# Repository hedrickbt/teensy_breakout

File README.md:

# teensy_breakout
CE Breakout board for the Teensy 3.2

.

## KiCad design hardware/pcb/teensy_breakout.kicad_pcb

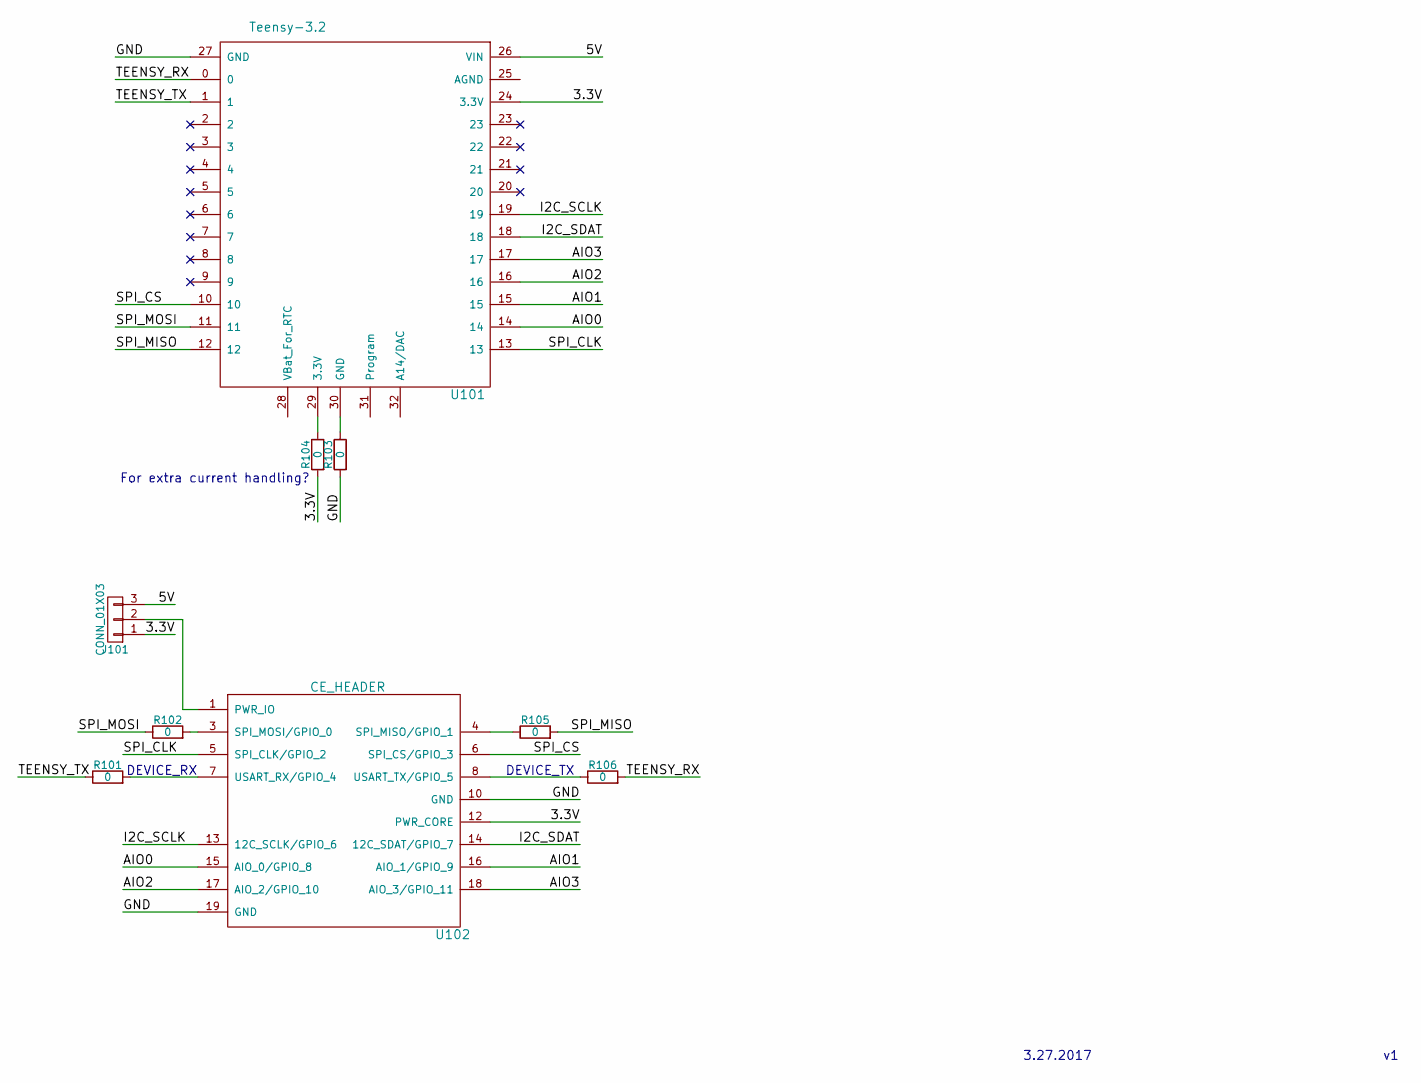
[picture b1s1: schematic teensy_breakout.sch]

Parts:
J101: CONN_01X03; Pin_Header_Straight_1x03_Pitch2.54mm
R101, R102, R103, R104, R105, R106: 0; R_0805
U101: Teensy-3.2; Teensy-32
U102: CE_HEADER

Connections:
/3.3V: J101.1, R104.2, U101.24 (3.3V), U102.12 (PWR_CORE)
/5V: J101.3, U101.26 (VIN)
/AIO0: U101.14, U102.15 (AIO_0/GPIO_8)
/AIO1: U101.15, U102.16 (AIO_1/GPIO_9)
/AIO2: U101.16, U102.17 (AIO_2/GPIO_10)
/AIO3: U101.17, U102.18 (AIO_3/GPIO_11)
/GND: R103.2, U101.27 (GND), U102.10 (GND), U102.19 (GND)
/I2C_SCLK: U101.19, U102.13 (12C_SCLK/GPIO_6)
/I2C_SDAT: U101.18, U102.14 (12C_SDAT/GPIO_7)
/SPI_CLK: U101.13, U102.5 (SPI_CLK/GPIO_2)
/SPI_CS: U101.10, U102.6 (SPI_CS/GPIO_3)
/SPI_MISO: R105.2, U101.12
/SPI_MOSI: R102.1, U101.11
/TEENSY_RX: R106.2, U101.0
/TEENSY_TX: R101.1, U101.1
unnamed: J101.2, U102.1 (PWR_IO)
unnamed: R101.2, U102.7 (USART_RX/GPIO_4)
unnamed: R102.2, U102.3 (SPI_MOSI/GPIO_0)
unnamed: R103.1, U101.30 (GND)
unnamed: R104.1, U101.29 (3.3V)
unnamed: R105.1, U102.4 (SPI_MISO/GPIO_1)
unnamed: R106.1, U102.8 (USART_TX/GPIO_5)

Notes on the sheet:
3.27.2017
DEVICE_TX
DEVICE_RX
For extra current handling?

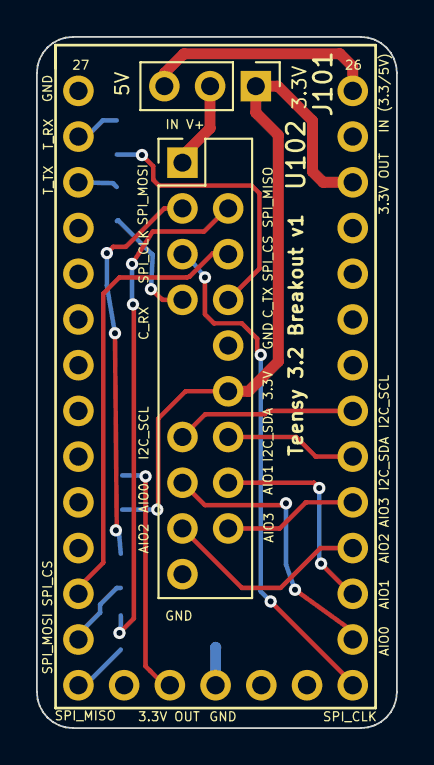
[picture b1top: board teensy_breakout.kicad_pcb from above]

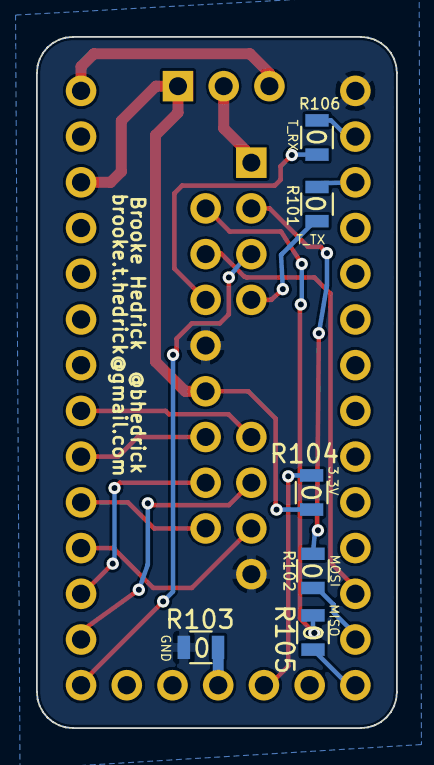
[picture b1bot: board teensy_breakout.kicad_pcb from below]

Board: 2 copper layers, 20.0 x 38.4 mm, 9 parts (6 on the bottom side), 22 nets.

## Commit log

2017-05-16 initial
2017-05-16 small update
